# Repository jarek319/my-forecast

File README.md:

# my-forecast
A simple way to check the day's weather

The "worst possible" weather for the next 8 hours is rendered using an 8x8 RGB LED matrix.

The animations need a bit of work...

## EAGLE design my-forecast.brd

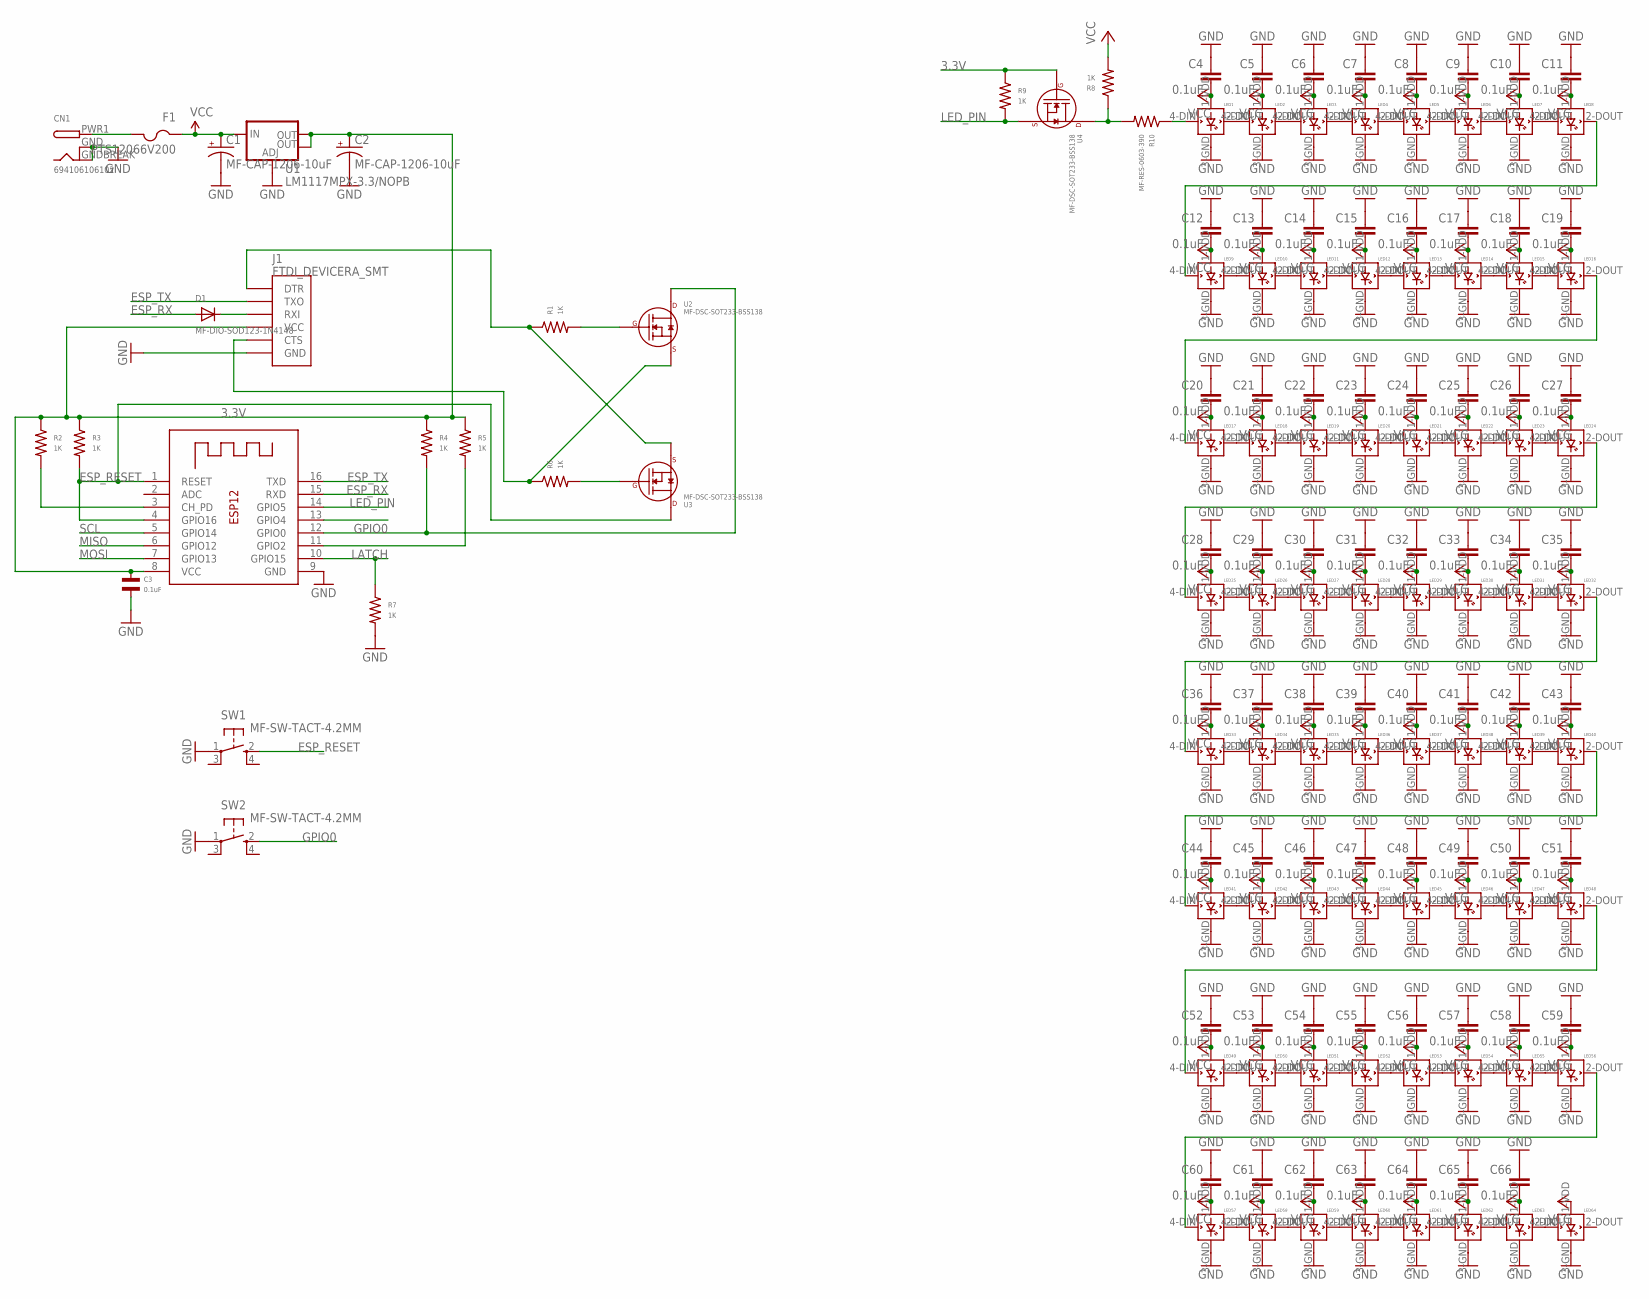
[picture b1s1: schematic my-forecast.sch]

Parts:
C1, C2: MF-CAP-1206-10uF; EIA3216
C3: 0.1uF; C0603
C4, C5, C6, C7, C8, C9, C10, C11, C12, C13, C14, C15, C16, C17, C18, C19, C20, C21, C22, C23, C24, C25, C26, C27, C28, C29, C30, C31, C32, C33, C34, C35, C36, C37, C38, C39, C40, C41, C42, C43, C44, C45, C46, C47, C48, C49, C50, C51, C52, C53, C54, C55, C56, C57, C58, C59, C60, C61, C62, C63, C64, C65, C66: 0.1uF; 0603-CAP
CN1: 694106106102; DCJACK_2MM_SMT
D1: MF-DIO-SOD123-1N4148; SOD-123
F1: PTS12066V200; R1206
J1: FTDI_DEVICERA_SMT; FTDI_DEVICE_RA_SMT
LED1, LED2, LED3, LED4, LED5, LED6, LED7, LED8, LED9, LED10, LED11, LED12, LED13, LED14, LED15, LED16, LED17, LED18, LED19, LED20, LED21, LED22, LED23, LED24, LED25, LED26, LED27, LED28, LED29, LED30, LED31, LED32, LED33, LED34, LED35, LED36, LED37, LED38, LED39, LED40, LED41, LED42, LED43, LED44, LED45, LED46, LED47, LED48, LED49, LED50, LED51, LED52, LED53, LED54, LED55, LED56, LED57, LED58, LED59, LED60, LED61, LED62, LED63, LED64: WS2812B5050; WS2812B
R1, R2, R3, R4, R5, R6, R7, R8, R9: 1K; R0603
R10: MF-RES-0603-390; R0603
SW1, SW2: MF-SW-TACT-4.2MM; KMR2
U1: LM1117MPX-3.3/NOPB; SOT223
U2, U3, U4: MF-DSC-SOT233-BSS138; SOT-23-3
X1: ESP-12

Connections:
3.3V: C2.A (+), C3.P$1, J1.4 (VCC), R2.P$1, R3.P$1, R4.P$1, R5.P$1, R9.P$1, U1.2 (OUT), U1.4 (OUT), U4.P$1 (GATE), X1.8 (VCC)
DIN: LED8.2-DOUT (DOUT), LED9.4-DIN (DIN)
DOUT: LED7.2-DOUT (DOUT), LED8.4-DIN (DIN)
ESP_RESET: R3.P$2, SW1.2 (S), U3.P$3 (DRAIN), X1.1 (RESET), X1.4 (GPIO16)
ESP_RX: D1.A, X1.15 (RXD)
ESP_TX: J1.2 (TXO), X1.16 (TXD)
GND: C1.C (-), C2.C (-), C3.P$2, C4.1, C5.1, C6.1, C7.1, C8.1, C9.1, C10.1, C11.1, C12.1, C13.1, C14.1, C15.1, C16.1, C17.1, C18.1, C19.1, C20.1, C21.1, C22.1, C23.1, C24.1, C25.1, C26.1, C27.1, C28.1, C29.1, C30.1, C31.1, C32.1, C33.1, C34.1, C35.1, C36.1, C37.1, C38.1, C39.1, C40.1, C41.1, C42.1, C43.1, C44.1, C45.1, C46.1, C47.1, C48.1, C49.1, C50.1, C51.1, C52.1, C53.1, C54.1, C55.1, C56.1, C57.1, C58.1, C59.1, C60.1, C61.1, C62.1, C63.1, C64.1, C65.1, C66.1, CN1.GND (GNDBREAK), CN1.GNDBREAK (GND), J1.6 (GND), LED1.3-GND (GND), LED2.3-GND (GND), LED3.3-GND (GND), LED4.3-GND (GND), LED5.3-GND (GND), LED6.3-GND (GND), LED7.3-GND (GND), LED8.3-GND (GND), LED9.3-GND (GND), LED10.3-GND (GND), LED11.3-GND (GND), LED12.3-GND (GND), LED13.3-GND (GND), LED14.3-GND (GND), LED15.3-GND (GND), LED16.3-GND (GND), LED17.3-GND (GND), LED18.3-GND (GND), LED19.3-GND (GND), LED20.3-GND (GND), LED21.3-GND (GND), LED22.3-GND (GND), LED23.3-GND (GND), LED24.3-GND (GND), LED25.3-GND (GND), LED26.3-GND (GND), LED27.3-GND (GND), LED28.3-GND (GND), LED29.3-GND (GND), LED30.3-GND (GND), LED31.3-GND (GND), LED32.3-GND (GND), LED33.3-GND (GND), LED34.3-GND (GND), LED35.3-GND (GND), LED36.3-GND (GND), LED37.3-GND (GND), LED38.3-GND (GND), LED39.3-GND (GND), LED40.3-GND (GND), LED41.3-GND (GND), LED42.3-GND (GND), LED43.3-GND (GND), LED44.3-GND (GND), LED45.3-GND (GND), LED46.3-GND (GND), LED47.3-GND (GND), LED48.3-GND (GND), LED49.3-GND (GND), LED50.3-GND (GND), LED51.3-GND (GND), LED52.3-GND (GND), LED53.3-GND (GND), LED54.3-GND (GND), LED55.3-GND (GND), LED56.3-GND (GND), LED57.3-GND (GND), LED58.3-GND (GND), LED59.3-GND (GND), LED60.3-GND (GND), LED61.3-GND (GND), LED62.3-GND (GND), LED63.3-GND (GND), LED64.3-GND (GND), R7.P$2, SW1.1, SW2.1, U1.1 (ADJ), X1.9 (GND)
GPIO0: R4.P$2, SW2.2 (S), U2.P$3 (DRAIN), X1.12 (GPIO0)
LATCH: R7.P$1, X1.10 (GPIO15)
LED_PIN: R9.P$2, U4.P$2 (SOURCE), X1.14 (GPIO5)
MISO: X1.6 (GPIO12)
MOSI: X1.7 (GPIO13)
unnamed: LED1.4-DIN (DIN), R10.P$1
unnamed: R8.P$1, R10.P$2, U4.P$3 (DRAIN)
unnamed: CN1.PWR1 (PWR), F1.2
unnamed: LED1.2-DOUT (DOUT), LED2.4-DIN (DIN)
unnamed: LED2.2-DOUT (DOUT), LED3.4-DIN (DIN)
unnamed: LED3.2-DOUT (DOUT), LED4.4-DIN (DIN)
unnamed: LED4.2-DOUT (DOUT), LED5.4-DIN (DIN)
unnamed: LED5.2-DOUT (DOUT), LED6.4-DIN (DIN)
unnamed: LED6.2-DOUT (DOUT), LED7.4-DIN (DIN)
unnamed: LED9.2-DOUT (DOUT), LED10.4-DIN (DIN)
unnamed: LED10.2-DOUT (DOUT), LED11.4-DIN (DIN)
unnamed: LED11.2-DOUT (DOUT), LED12.4-DIN (DIN)
unnamed: LED12.2-DOUT (DOUT), LED13.4-DIN (DIN)
unnamed: LED13.2-DOUT (DOUT), LED14.4-DIN (DIN)
unnamed: LED14.2-DOUT (DOUT), LED15.4-DIN (DIN)
unnamed: LED15.2-DOUT (DOUT), LED16.4-DIN (DIN)
unnamed: LED16.2-DOUT (DOUT), LED17.4-DIN (DIN)
unnamed: LED24.2-DOUT (DOUT), LED25.4-DIN (DIN)
unnamed: LED33.2-DOUT (DOUT), LED34.4-DIN (DIN)
unnamed: LED34.2-DOUT (DOUT), LED35.4-DIN (DIN)
unnamed: LED35.2-DOUT (DOUT), LED36.4-DIN (DIN)
unnamed: LED36.2-DOUT (DOUT), LED37.4-DIN (DIN)
unnamed: LED37.2-DOUT (DOUT), LED38.4-DIN (DIN)
unnamed: LED38.2-DOUT (DOUT), LED39.4-DIN (DIN)
unnamed: LED39.2-DOUT (DOUT), LED40.4-DIN (DIN)
unnamed: LED41.2-DOUT (DOUT), LED42.4-DIN (DIN)
unnamed: LED42.2-DOUT (DOUT), LED43.4-DIN (DIN)
unnamed: LED43.2-DOUT (DOUT), LED44.4-DIN (DIN)
unnamed: LED44.2-DOUT (DOUT), LED45.4-DIN (DIN)
unnamed: LED45.2-DOUT (DOUT), LED46.4-DIN (DIN)
unnamed: LED46.2-DOUT (DOUT), LED47.4-DIN (DIN)
unnamed: LED47.2-DOUT (DOUT), LED48.4-DIN (DIN)
unnamed: LED40.2-DOUT (DOUT), LED41.4-DIN (DIN)
unnamed: LED48.2-DOUT (DOUT), LED49.4-DIN (DIN)
unnamed: LED56.2-DOUT (DOUT), LED57.4-DIN (DIN)
unnamed: LED32.2-DOUT (DOUT), LED33.4-DIN (DIN)
unnamed: LED25.2-DOUT (DOUT), LED26.4-DIN (DIN)
unnamed: LED26.2-DOUT (DOUT), LED27.4-DIN (DIN)
unnamed: LED27.2-DOUT (DOUT), LED28.4-DIN (DIN)
unnamed: LED28.2-DOUT (DOUT), LED29.4-DIN (DIN)
unnamed: LED29.2-DOUT (DOUT), LED30.4-DIN (DIN)
unnamed: LED30.2-DOUT (DOUT), LED31.4-DIN (DIN)
unnamed: LED31.2-DOUT (DOUT), LED32.4-DIN (DIN)
unnamed: LED49.2-DOUT (DOUT), LED50.4-DIN (DIN)
unnamed: LED50.2-DOUT (DOUT), LED51.4-DIN (DIN)
unnamed: LED51.2-DOUT (DOUT), LED52.4-DIN (DIN)
unnamed: LED52.2-DOUT (DOUT), LED53.4-DIN (DIN)
unnamed: LED53.2-DOUT (DOUT), LED54.4-DIN (DIN)
unnamed: LED54.2-DOUT (DOUT), LED55.4-DIN (DIN)
unnamed: LED55.2-DOUT (DOUT), LED56.4-DIN (DIN)
unnamed: LED57.2-DOUT (DOUT), LED58.4-DIN (DIN)
unnamed: LED58.2-DOUT (DOUT), LED59.4-DIN (DIN)
unnamed: LED59.2-DOUT (DOUT), LED60.4-DIN (DIN)
unnamed: LED60.2-DOUT (DOUT), LED61.4-DIN (DIN)
unnamed: LED61.2-DOUT (DOUT), LED62.4-DIN (DIN)
unnamed: LED62.2-DOUT (DOUT), LED63.4-DIN (DIN)
unnamed: LED63.2-DOUT (DOUT), LED64.4-DIN (DIN)
unnamed: LED17.2-DOUT (DOUT), LED18.4-DIN (DIN)
unnamed: LED18.2-DOUT (DOUT), LED19.4-DIN (DIN)
unnamed: LED19.2-DOUT (DOUT), LED20.4-DIN (DIN)
unnamed: LED20.2-DOUT (DOUT), LED21.4-DIN (DIN)
unnamed: LED21.2-DOUT (DOUT), LED22.4-DIN (DIN)
unnamed: LED22.2-DOUT (DOUT), LED23.4-DIN (DIN)
unnamed: LED23.2-DOUT (DOUT), LED24.4-DIN (DIN)
unnamed: R6.P$2, U3.P$1 (GATE)
unnamed: R1.P$2, U2.P$1 (GATE)
unnamed: J1.5 (CTS), R6.P$1, U2.P$2 (SOURCE)
unnamed: R2.P$2, X1.3 (CH_PD)
unnamed: J1.1 (DTR), R1.P$1, U3.P$2 (SOURCE)
unnamed: D1.C, J1.3 (RXI)
unnamed: R5.P$2, X1.11 (GPIO2)
SCL: X1.5 (GPIO14)
VCC: C1.A (+), C4.2, C5.2, C6.2, C7.2, C8.2, C9.2, C10.2, C11.2, C12.2, C13.2, C14.2, C15.2, C16.2, C17.2, C18.2, C19.2, C20.2, C21.2, C22.2, C23.2, C24.2, C25.2, C26.2, C27.2, C28.2, C29.2, C30.2, C31.2, C32.2, C33.2, C34.2, C35.2, C36.2, C37.2, C38.2, C39.2, C40.2, C41.2, C42.2, C43.2, C44.2, C45.2, C46.2, C47.2, C48.2, C49.2, C50.2, C51.2, C52.2, C53.2, C54.2, C55.2, C56.2, C57.2, C58.2, C59.2, C60.2, C61.2, C62.2, C63.2, C64.2, C65.2, C66.2, F1.1, LED1.1-VDD (VDD), LED2.1-VDD (VDD), LED3.1-VDD (VDD), LED4.1-VDD (VDD), LED5.1-VDD (VDD), LED6.1-VDD (VDD), LED7.1-VDD (VDD), LED8.1-VDD (VDD), LED9.1-VDD (VDD), LED10.1-VDD (VDD), LED11.1-VDD (VDD), LED12.1-VDD (VDD), LED13.1-VDD (VDD), LED14.1-VDD (VDD), LED15.1-VDD (VDD), LED16.1-VDD (VDD), LED17.1-VDD (VDD), LED18.1-VDD (VDD), LED19.1-VDD (VDD), LED20.1-VDD (VDD), LED21.1-VDD (VDD), LED22.1-VDD (VDD), LED23.1-VDD (VDD), LED24.1-VDD (VDD), LED25.1-VDD (VDD), LED26.1-VDD (VDD), LED27.1-VDD (VDD), LED28.1-VDD (VDD), LED29.1-VDD (VDD), LED30.1-VDD (VDD), LED31.1-VDD (VDD), LED32.1-VDD (VDD), LED33.1-VDD (VDD), LED34.1-VDD (VDD), LED35.1-VDD (VDD), LED36.1-VDD (VDD), LED37.1-VDD (VDD), LED38.1-VDD (VDD), LED39.1-VDD (VDD), LED40.1-VDD (VDD), LED41.1-VDD (VDD), LED42.1-VDD (VDD), LED43.1-VDD (VDD), LED44.1-VDD (VDD), LED45.1-VDD (VDD), LED46.1-VDD (VDD), LED47.1-VDD (VDD), LED48.1-VDD (VDD), LED49.1-VDD (VDD), LED50.1-VDD (VDD), LED51.1-VDD (VDD), LED52.1-VDD (VDD), LED53.1-VDD (VDD), LED54.1-VDD (VDD), LED55.1-VDD (VDD), LED56.1-VDD (VDD), LED57.1-VDD (VDD), LED58.1-VDD (VDD), LED59.1-VDD (VDD), LED60.1-VDD (VDD), LED61.1-VDD (VDD), LED62.1-VDD (VDD), LED63.1-VDD (VDD), LED64.1-VDD (VDD), R8.P$2, U1.3 (IN)

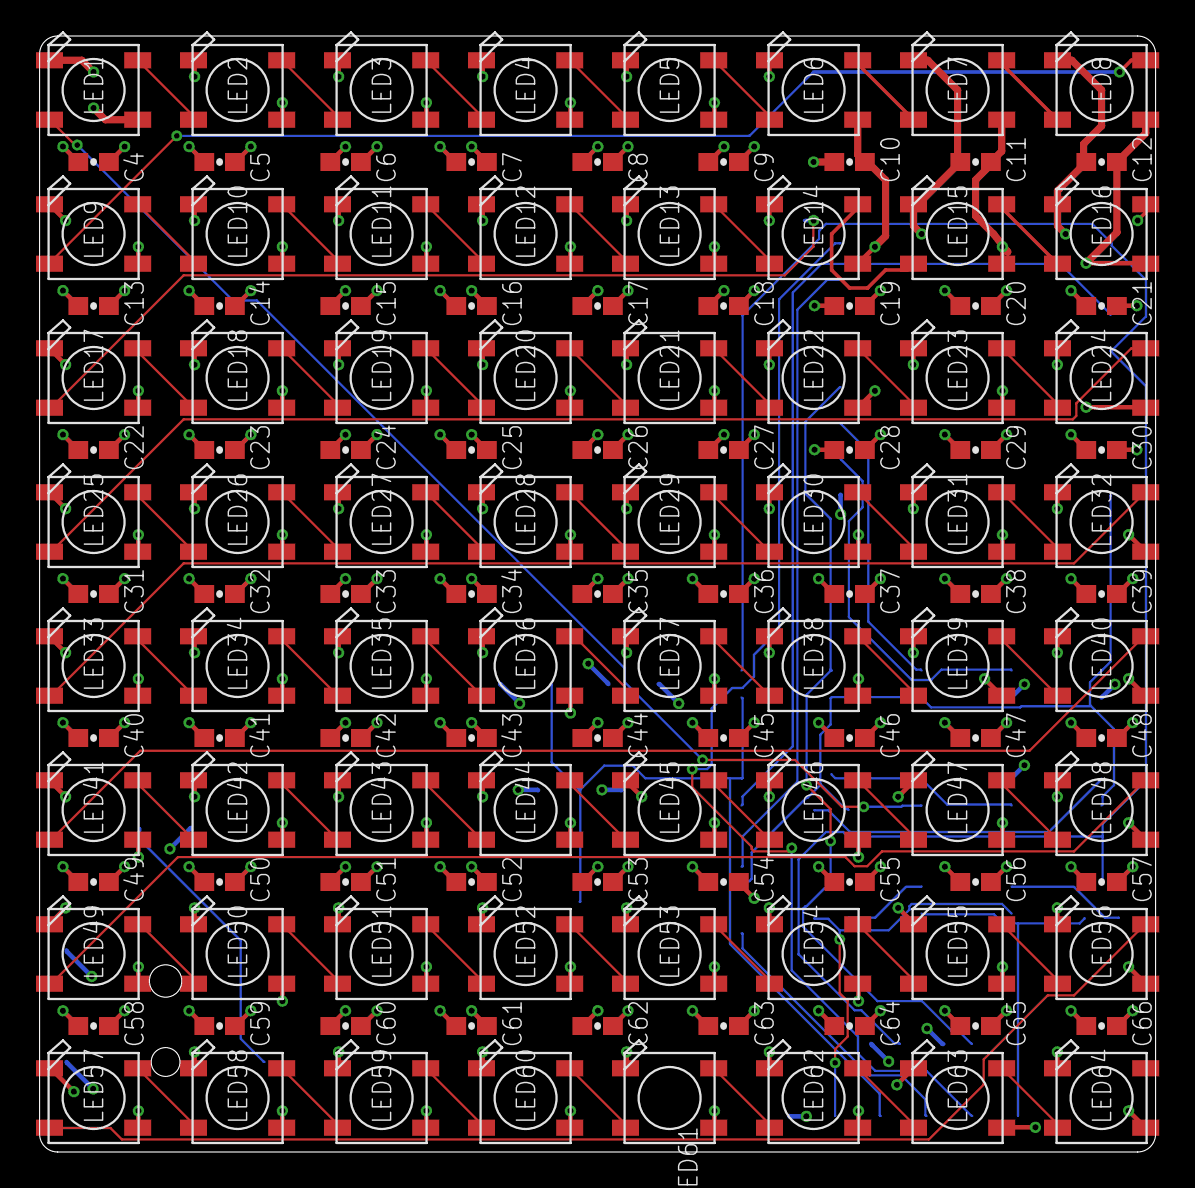
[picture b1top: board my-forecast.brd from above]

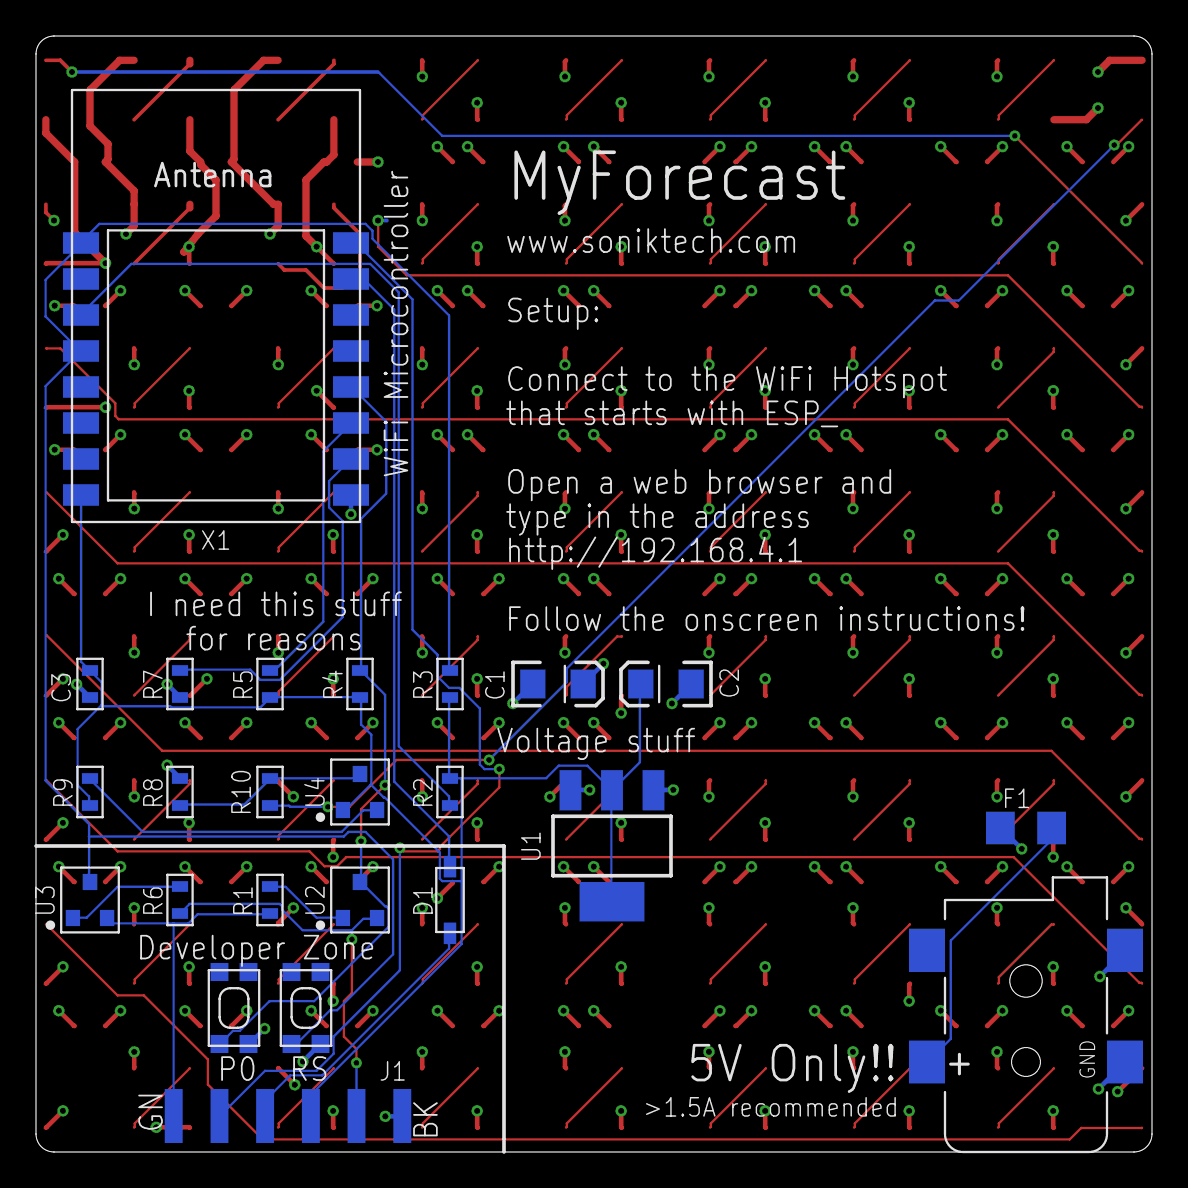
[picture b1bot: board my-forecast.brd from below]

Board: 4 copper layers, 62.0 x 62.0 mm, 151 parts (24 on the bottom side), 82 nets.

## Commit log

2018-07-05 design tested: working

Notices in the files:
parts and their libraries:
SparkFun-Capacitors: Licensing: CC v3.0 Share-Alike You are welcome to use this library for commercial purposes.
SparkFun-Connectors: Licensing: Creative Commons ShareAlike 4.0 International - https://creativecommons.org/licenses/by-sa/4.0
